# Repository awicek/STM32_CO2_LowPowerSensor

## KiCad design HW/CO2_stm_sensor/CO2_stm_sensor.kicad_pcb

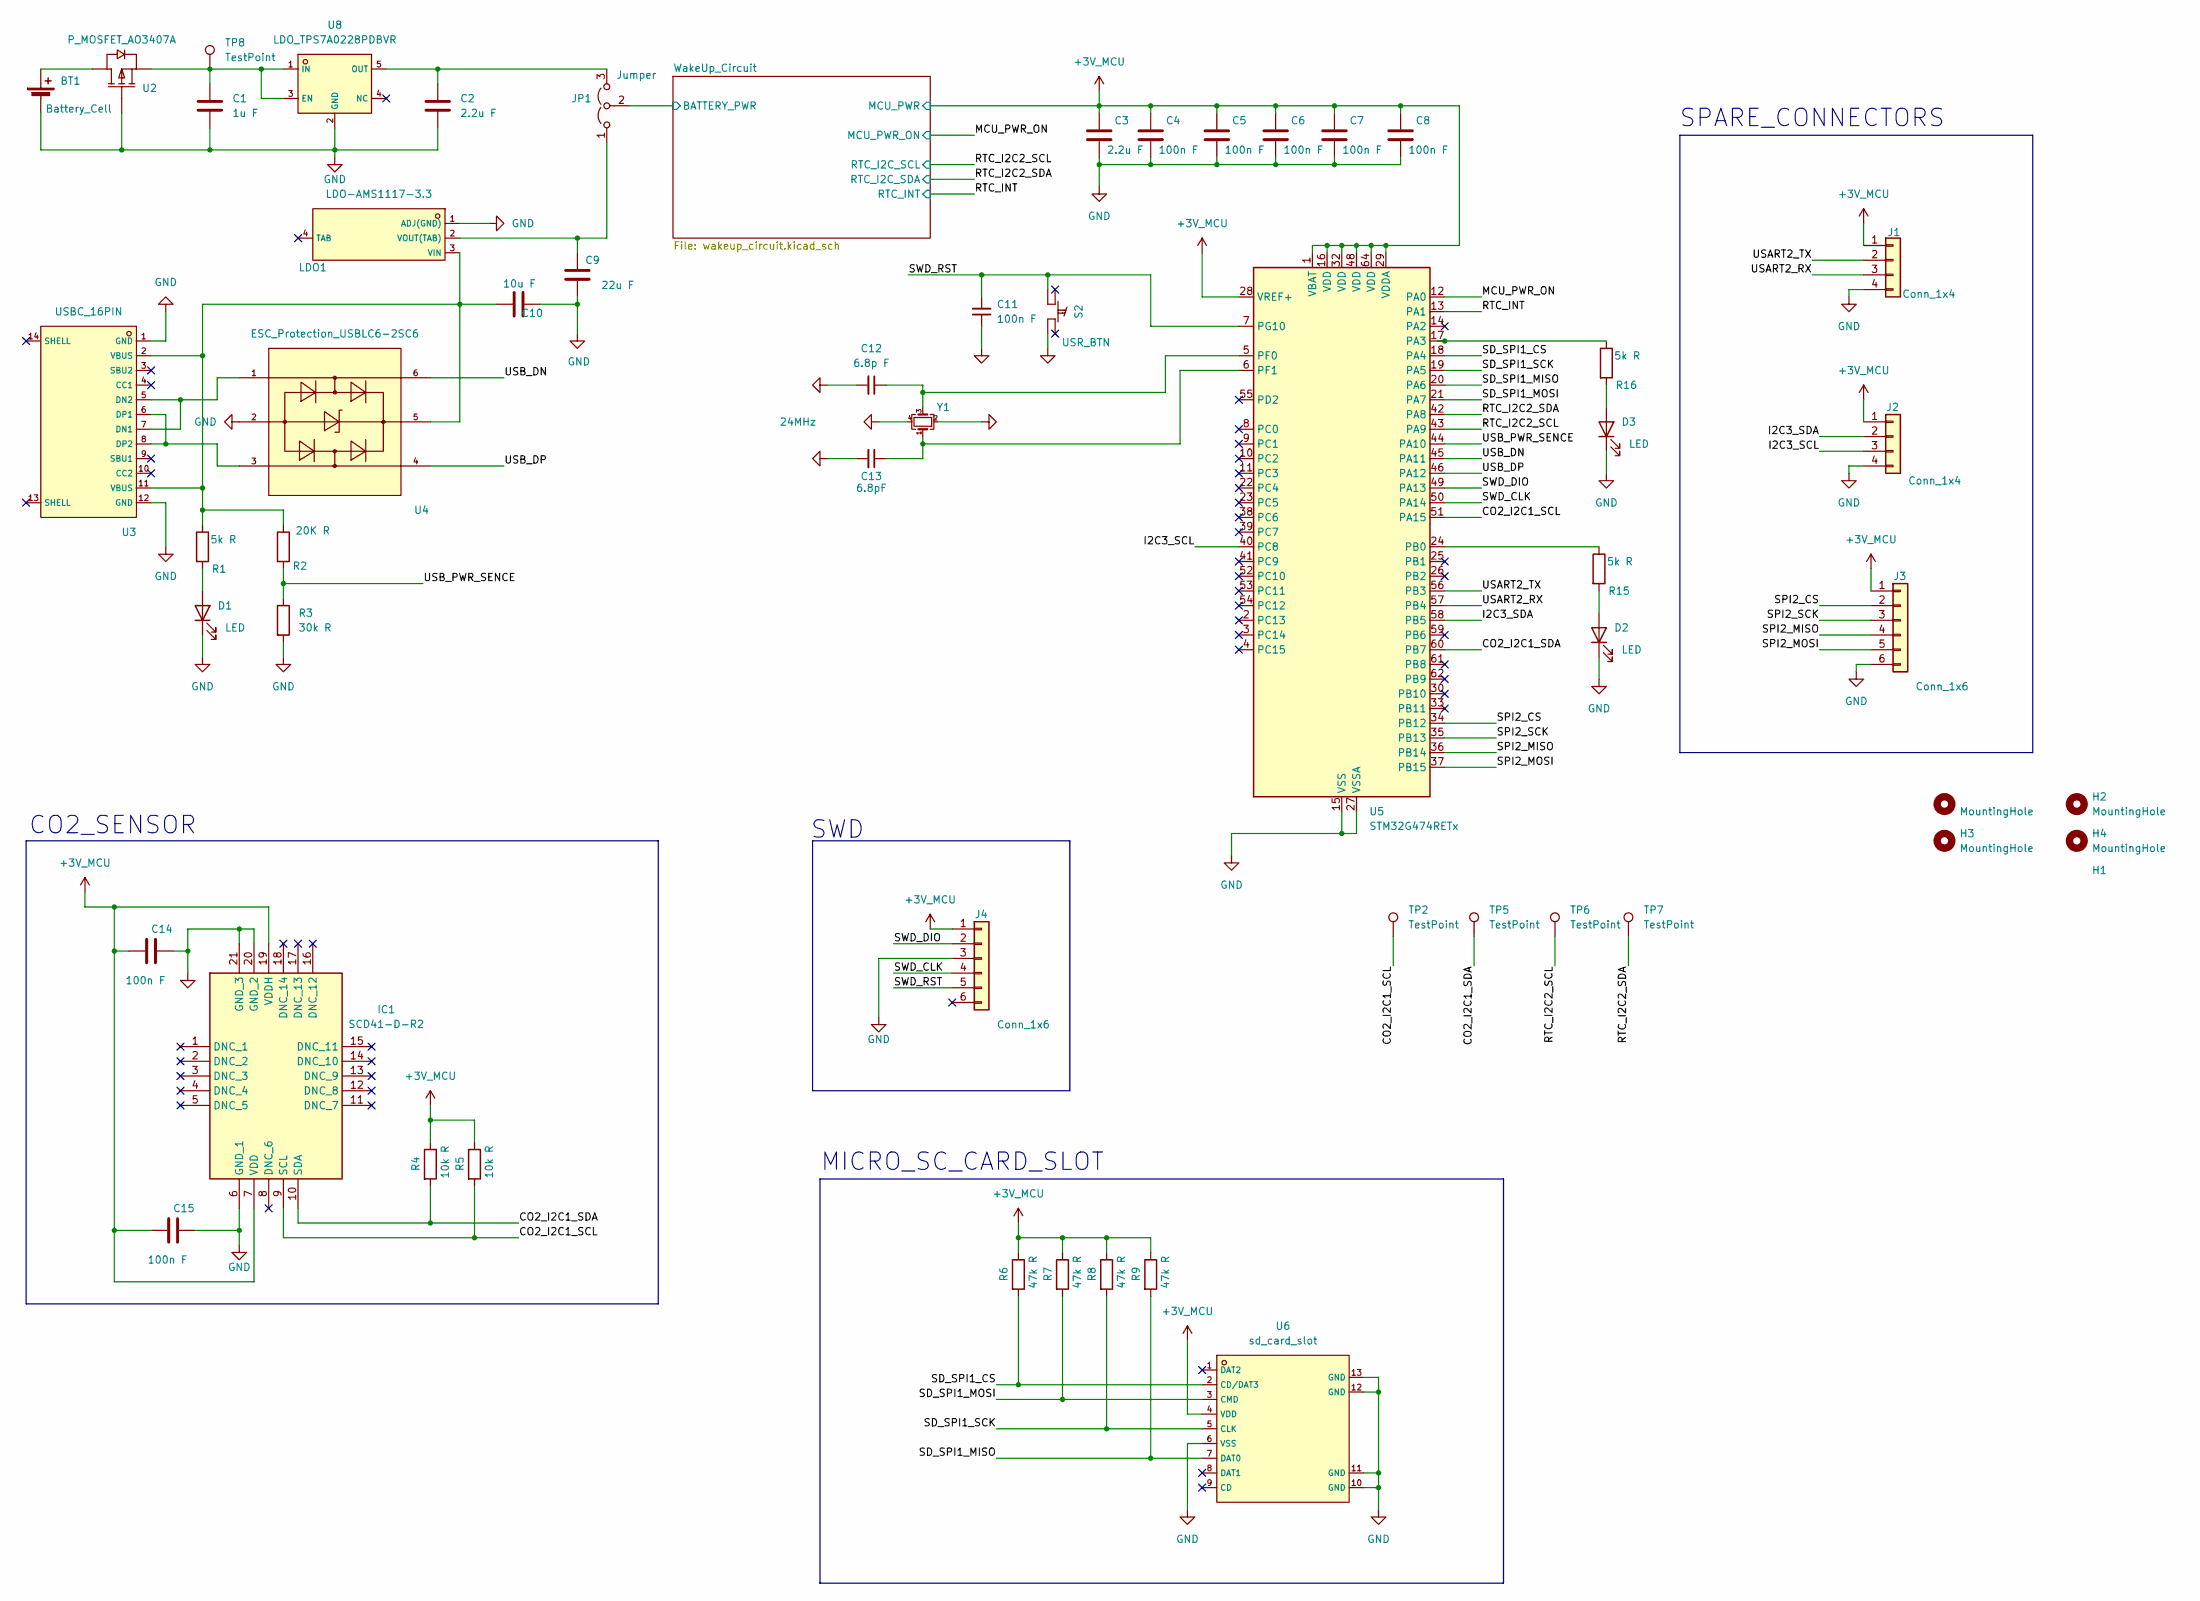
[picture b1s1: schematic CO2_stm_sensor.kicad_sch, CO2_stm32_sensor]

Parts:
BT1: Battery_Cell; BATTERY-SMD_18650-1S-L77.1-W20.7-1; LCSC Part # C7525438
C1: 1u F; C_0805_2012Metric_Pad1.18x1.45mm_HandSolder
C2, C3: 2.2u F; C_0805_2012Metric_Pad1.18x1.45mm_HandSolder
C4, C5, C6, C7, C8, C14, C15: 100n F; C_0805_2012Metric_Pad1.18x1.45mm_HandSolder
C9: 22u F; C_0805_2012Metric_Pad1.18x1.45mm_HandSolder
C10: 10u F; C_0805_2012Metric_Pad1.18x1.45mm_HandSolder
C11: 100n F; C_0805_2012Metric_Pad1.18x1.45mm_HandSolder; Mouser Part Number 80-C0805C104Z3V
C12: 6.8p F; C_0603_1608Metric_Pad1.08x0.95mm_HandSolder; LCSC Part # C1679
C13: 6.8pF; C_0603_1608Metric_Pad1.08x0.95mm_HandSolder; LCSC Part # C1679
D1, D2, D3: LED; LED_0805_2012Metric_Pad1.15x1.40mm_HandSolder
H1, H2, H3, H4: MountingHole; MountingHole_4mm
IC1: SCD41-D-R2; SCD41DR2
J1, J2: Conn_1x4; CONN-TH_4P-P2.00_S4B-PH-K-S-LF-SN; LCSC Part # C157926
J3, J4: Conn_1x6; CONN-TH_6P-P2.00_S6B-PH-K-S-LF-SN; LCSC Part # C157920
JP1: Jumper; PinHeader_1x03_P2.54mm_Vertical
LDO1: LDO-AMS1117-3.3; SOT-223-4_L6.5-W3.5-P2.30-LS7.0-BR; LCSC C347222
R1, R15, R16: 5k R; R_0805_2012Metric
R2: 20K R; R_0805_2012Metric
R3: 30k R; R_0805_2012Metric
R4, R5: 10k R; R_0805_2012Metric
R6, R7, R8, R9: 47k R; R_0805_2012Metric
S2: USR_BTN; pushbutton_EVQPUC02K; LCSC Part # C79174
TP2, TP5, TP6, TP7, TP8: TestPoint; PinHeader_1x01_P2.54mm_Vertical
U2: P_MOSFET_AO3407A; SOT-23-3_L2.9-W1.6-P1.90-LS2.8-BR; LCSC C15155
U3: USBC_16PIN; USB-C-SMD_TYPE-C-6PIN-2MD-073; LCSC C2765186
U4: ESC_Protection_USBLC6-2SC6; SOT-23-6_L2.9-W1.6-P0.95-LS2.8-BL; LCSC C7519
U5: STM32G474RETx; LQFP-64_10x10mm_P0.5mm; LCSC Part # C521608
U6: sd_card_slot; TF-SMD_TF-CARD-H1.8; LCSC C7529389
U8: LDO_TPS7A0228PDBVR; SOT-23-5_L2.9-W1.6-P0.95-LS2.8-BR; LCSC C5220176
Y1: 24MHz; CRYSTAL-SMD_4P-L2.0-W1.6-BL; LCSC Part # C37635325

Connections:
+3V_MCU: C3.1, C4.1, C5.1, C6.1, C7.1, C8.1, C14.1, C15.1, IC1.7 (VDD), IC1.19 (VDDH), J1.1, J2.1, J3.1, J4.1, R4.1, R5.1, R6.1, R7.1, R8.1, R9.1, U5.1 (VBAT), U5.16 (VDD), U5.28 (VREF+), U5.29 (VDDA), U5.32 (VDD), U5.48 (VDD), U5.64 (VDD), U6.4 (VDD); also elsewhere on the board
/CO2_I2C1_SCL: IC1.9 (SCL), R5.2, TP2.1, U5.51 (PA15)
/CO2_I2C1_SDA: IC1.10 (SDA), R4.2, TP5.1, U5.60 (PB7)
/I2C3_SCL: J2.3, U5.40 (PC8)
/I2C3_SDA: J2.2, U5.58 (PB5)
/MCU_PWR_ON: U5.12 (PA0); also elsewhere on the board
/RTC_I2C2_SCL: TP6.1, U5.43 (PA9); also elsewhere on the board
/RTC_I2C2_SDA: TP7.1, U5.42 (PA8); also elsewhere on the board
/RTC_INT: U5.13 (PA1); also elsewhere on the board
/SD_SPI1_CS: R6.2, U5.18 (PA4), U6.2 (CD/DAT3)
/SD_SPI1_MISO: R9.2, U5.20 (PA6), U6.7 (DAT0)
/SD_SPI1_MOSI: R7.2, U5.21 (PA7), U6.3 (CMD)
/SD_SPI1_SCK: R8.2, U5.19 (PA5), U6.5 (CLK)
/SPI2_CS: J3.2, U5.34 (PB12)
/SPI2_MISO: J3.4, U5.36 (PB14)
/SPI2_MOSI: J3.5, U5.37 (PB15)
/SPI2_SCK: J3.3, U5.35 (PB13)
/SWD_CLK: J4.4, U5.50 (PA14)
/SWD_DIO: J4.2, U5.49 (PA13)
/SWD_RST: C11.2, J4.5, S2.2, U5.7 (PG10)
/USART2_RX: J1.3, U5.57 (PB4)
/USART2_TX: J1.2, U5.56 (PB3)
/USB_DN: U4.6, U5.45 (PA11)
/USB_DP: U4.4, U5.46 (PA12)
/USB_PWR_SENCE: R2.2, R3.1, U5.44 (PA10)
/WakeUp_Circuit/BATTERY_PWR: JP1.2 (C); also elsewhere on the board
GND: BT1.2 (-), C1.2, C2.2, C3.2, C4.2, C5.2, C6.2, C7.2, C8.2, C9.2, C10.2, C11.1, C12.2, C13.2, C14.2, C15.2, D1.1 (K), D2.1 (K), D3.1 (K), IC1.6 (GND_1), IC1.20 (GND_2), IC1.21 (GND_3), J1.4, J2.4, J3.6, J4.3, LDO1.1 (ADJ(GND)), R3.2, S2.4, U2.1 (G), U3.1 (GND), U3.12 (GND), U4.2, U5.15 (VSS), U5.27 (VSSA), U5.31 (VSS), U5.47 (VSS), U5.63 (VSS), U6.6 (VSS), U6.10 (GND), U6.11 (GND), U6.12 (GND), U6.13 (GND), U8.2 (GND), Y1.2, Y1.4; also elsewhere on the board
unnamed: BT1.1 (+), U2.3 (D)
unnamed: D1.2 (A), R1.2
unnamed: D2.2 (A), R15.2
unnamed: D3.2 (A), R16.2
unnamed: C9.1, JP1.1 (A), LDO1.2 (VOUT(TAB))
unnamed: C2.1, JP1.3 (B), U8.5 (OUT)
unnamed: C10.1, LDO1.3 (VIN), R1.1, R2.1, U3.2 (VBUS), U3.11 (VBUS), U4.5
unnamed: C1.1, TP8.1, U2.2 (S), U8.1 (IN), U8.3 (EN)
unnamed: U3.5 (DN2), U3.7 (DN1), U4.1
unnamed: U3.6 (DP1), U3.8 (DP2), U4.3
unnamed: R16.1, U5.17 (PA3)
unnamed: R15.1, U5.24 (PB0)
unnamed: C12.1, U5.5 (PF0), Y1.3
unnamed: C13.1, U5.6 (PF1), Y1.1

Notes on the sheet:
SWD
MICRO_SC_CARD_SLOT
SPARE_CONNECTORS
CO2_SENSOR

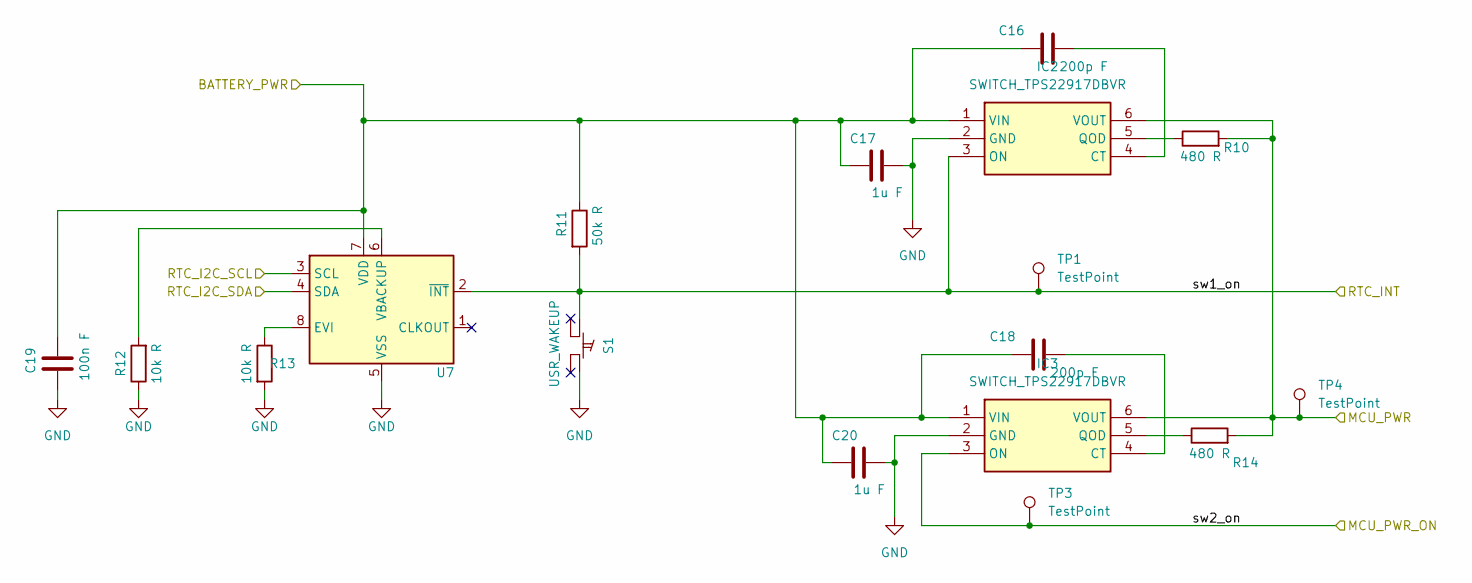
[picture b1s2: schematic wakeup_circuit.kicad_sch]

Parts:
C16, C18: 200p F; C_0805_2012Metric_Pad1.18x1.45mm_HandSolder
C17, C20: 1u F; C_0805_2012Metric_Pad1.18x1.45mm_HandSolder
C19: 100n F; C_0805_2012Metric_Pad1.18x1.45mm_HandSolder
IC2: SWITCH_TPS22917DBVR; SOT95P280X145-6N
IC3: SWITCH_TPS22917DBVR; SOT95P280X145-6N; Mouser Part Number 595-TPS22917DBVR
R10, R14: 480 R; R_0805_2012Metric
R11: 50k R; R_0805_2012Metric
R12, R13: 10k R; R_0805_2012Metric
S1: USR_WAKEUP; pushbutton_EVQPUC02K; LCSC Part # C79174
TP1, TP3, TP4: TestPoint; PinHeader_1x01_P2.54mm_Vertical
U7: MicroCrystal_C7_SON-8_1.5x3.2mm_P0.9mm

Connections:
+3V_MCU: IC2.6 (VOUT), IC3.6 (VOUT), R10.2, R14.2, TP4.1; also elsewhere on the board
/MCU_PWR_ON: IC3.3 (ON), TP3.1; also elsewhere on the board
/RTC_I2C2_SCL: U7.3 (SCL); also elsewhere on the board
/RTC_I2C2_SDA: U7.4 (SDA); also elsewhere on the board
/RTC_INT: IC2.3 (ON), R11.2, S1.1, TP1.1, U7.2 (~INT); also elsewhere on the board
/WakeUp_Circuit/BATTERY_PWR: C16.1, C17.1, C18.1, C19.1, C20.1, IC2.1 (VIN), IC3.1 (VIN), R11.1, U7.7 (VDD); also elsewhere on the board
GND: C17.2, C19.2, C20.2, IC2.2 (GND), IC3.2 (GND), R12.1, R13.2, S1.3, U7.5 (VSS); also elsewhere on the board
unnamed: C16.2, IC2.4 (CT)
unnamed: IC2.5 (QOD), R10.1
unnamed: C18.2, IC3.4 (CT)
unnamed: IC3.5 (QOD), R14.1
unnamed: R13.1, U7.8 (EVI)
unnamed: R12.2, U7.6 (VBACKUP)

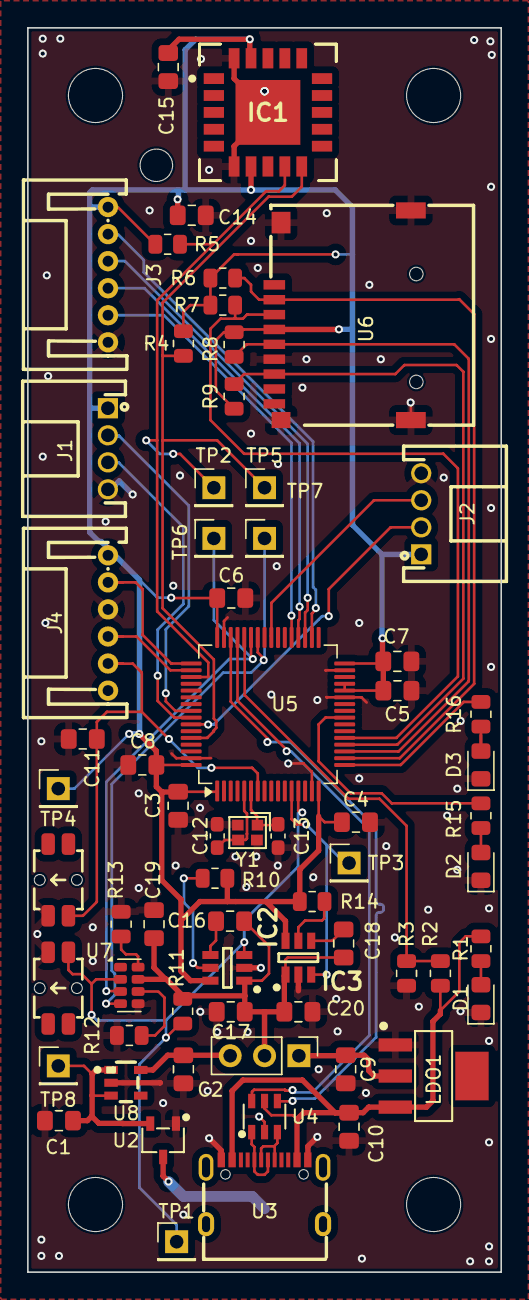
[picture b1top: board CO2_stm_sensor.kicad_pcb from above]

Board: 2 copper layers, 35.0 x 92.0 mm, 71 parts (1 on the bottom side), 47 nets.

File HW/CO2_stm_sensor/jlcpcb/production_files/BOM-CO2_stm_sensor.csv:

Comment,Designator,Footprint,LCSC,Quantity
100n F,C5,C_0805_2012Metric_Pad1.18x1.45mm_HandSolder,C49678,1
10k R,R4,R_0805_2012Metric,C17414,1
10u F,C10,C_0805_2012Metric_Pad1.18x1.45mm_HandSolder,C15850,1
1u F,C1,C_0805_2012Metric_Pad1.18x1.45mm_HandSolder,C28323,1
2.2u F,C2,C_0805_2012Metric_Pad1.18x1.45mm_HandSolder,C377773,1
200p F,C16,C_0805_2012Metric_Pad1.18x1.45mm_HandSolder,C1724,1
20K R,R2,R_0805_2012Metric,C4328,1
22u F,C9,C_0805_2012Metric_Pad1.18x1.45mm_HandSolder,C45783,1
24MHz,Y1,CRYSTAL-SMD_4P-L2.0-W1.6-BL,C37635325,1
30k R,R3,R_0805_2012Metric,C17621,1
47k R,R6,R_0805_2012Metric,C17713,1
480 R,R10,R_0805_2012Metric,C17710,1
5k R,R15,R_0805_2012Metric,C17673,1
6.8p F,C12,C_0603_1608Metric_Pad1.08x0.95mm_HandSolder,C1679,1
6.8pF,C13,C_0603_1608Metric_Pad1.08x0.95mm_HandSolder,C1679,1
Battery_Cell,BT1,BATTERY-SMD_18650-1S-L77.1-W20.7-1,C7525438,1
Conn_1x4,"J1,J2",CONN-TH_4P-P2.00_S4B-PH-K-S-LF-SN,C157926,2
Conn_1x6,"J3,J4",CONN-TH_6P-P2.00_S6B-PH-K-S-LF-SN,C157920,2
ESC_Protection_USBLC6-2SC6,U4,SOT-23-6_L2.9-W1.6-P0.95-LS2.8-BL,C7519,1
LDO-AMS1117-3.3,LDO1,SOT-223-4_L6.5-W3.5-P2.30-LS7.0-BR,C347222,1
LDO_TPS7A0228PDBVR,U8,SOT-23-5_L2.9-W1.6-P0.95-LS2.8-BR,C5220176,1
P_MOSFET_AO3407A,U2,SOT-23-3_L2.9-W1.6-P1.90-LS2.8-BR,C15155,1
STM32G474RETx,U5,LQFP-64_10x10mm_P0.5mm,C521608,1
USBC_16PIN,U3,USB-C-SMD_TYPE-C-6PIN-2MD-073,C2765186,1
USR_BTN,S2,pushbutton_EVQPUC02K,C79174,1
USR_WAKEUP,S1,pushbutton_EVQPUC02K,C79174,1
sd_card_slot,U6,TF-SMD_TF-CARD-H1.8,C7529389,1
SCD41-D-R2,IC1,SCD41DR2,,1
SWITCH_TPS22917DBVR,IC3,SOT95P280X145-6N,,1
100n F,C8,C_0805_2012Metric_Pad1.18x1.45mm_HandSolder,,1
100n F,C7,C_0805_2012Metric_Pad1.18x1.45mm_HandSolder,,1
Jumper,JP1,PinHeader_1x03_P2.54mm_Vertical,,1
~,U7,MicroCrystal_C7_SON-8_1.5x3.2mm_P0.9mm,,1
100n F,C6,C_0805_2012Metric_Pad1.18x1.45mm_HandSolder,,1
2.2u F,C3,C_0805_2012Metric_Pad1.18x1.45mm_HandSolder,,1
100n F,C19,C_0805_2012Metric_Pad1.18x1.45mm_HandSolder,,1
1u F,C20,C_0805_2012Metric_Pad1.18x1.45mm_HandSolder,,1
47k R,R8,R_0805_2012Metric,,1
LED,D2,LED_0805_2012Metric_Pad1.15x1.40mm_HandSolder,,1
SWITCH_TPS22917DBVR,IC2,SOT95P280X145-6N,,1
100n F,C14,C_0805_2012Metric_Pad1.18x1.45mm_HandSolder,,1
1u F,C17,C_0805_2012Metric_Pad1.18x1.45mm_HandSolder,,1
47k R,R7,R_0805_2012Metric,,1
480 R,R14,R_0805_2012Metric,,1
10k R,R5,R_0805_2012Metric,,1
200p F,C18,C_0805_2012Metric_Pad1.18x1.45mm_HandSolder,,1
47k R,R9,R_0805_2012Metric,,1
100n F,C11,C_0805_2012Metric_Pad1.18x1.45mm_HandSolder,,1
LED,D1,LED_0805_2012Metric_Pad1.15x1.40mm_HandSolder,,1
2k R,R1,R_0805_2012Metric,,1
100n F,C4,C_0805_2012Metric_Pad1.18x1.45mm_HandSolder,,1
10k R,R13,R_0805_2012Metric,,1
100n F,C15,C_0805_2012Metric_Pad1.18x1.45mm_HandSolder,,1
50k R,R11,R_0805_2012Metric,,1
10k R,R12,R_0805_2012Metric,,1
TestPoint,TP8,PinHeader_1x01_P2.54mm_Vertical,,1
TestPoint,TP7,PinHeader_1x01_P2.54mm_Vertical,,1
TestPoint,TP6,PinHeader_1x01_P2.54mm_Vertical,,1
TestPoint,TP5,PinHeader_1x01_P2.54mm_Vertical,,1
TestPoint,TP4,PinHeader_1x01_P2.54mm_Vertical,,1
TestPoint,TP3,PinHeader_1x01_P2.54mm_Vertical,,1
TestPoint,TP2,PinHeader_1x01_P2.54mm_Vertical,,1
TestPoint,TP1,PinHeader_1x01_P2.54mm_Vertical,,1
5k R,R16,R_0805_2012Metric,,1
LED,D3,LED_0805_2012Metric_Pad1.15x1.40mm_HandSolder,,1

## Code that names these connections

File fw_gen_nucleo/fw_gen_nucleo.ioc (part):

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Mcu.Name=STM32G474R(B-C-E)Tx
Mcu.Package=LQFP64
Mcu.UserName=STM32G474RETx
PA13.GPIOParameters=GPIO_Label
PA13.GPIO_Label=T_SWDIO
PA13.Signal=SYS_JTMS-SWDIO
PA14.GPIOParameters=GPIO_Label
PA14.GPIO_Label=T_SWCLK
PA14.Signal=SYS_JTCK-SWCLK
PA15.Mode=I2C
PA15.Signal=I2C1_SCL
PA2.Mode=Asynchronous
PA2.Signal=USART2_TX
PA3.Mode=Asynchronous
PA3.Signal=USART2_RX
PA4.Signal=GPIO_Output
PA5.Mode=Full_Duplex_Master
PA5.Signal=SPI1_SCK
PA6.Mode=Full_Duplex_Master
PA6.Signal=SPI1_MISO
PA7.Mode=Full_Duplex_Master
PA7.Signal=SPI1_MOSI
PA8.Mode=I2C
PA8.Signal=I2C2_SDA
PB1.GPIOParameters=PinState,GPIO_PuPd
PB1.GPIO_PuPd=GPIO_PULLUP
PB1.PinState=GPIO_PIN_SET
PB1.Signal=GPIO_Output
PB3.GPIOParameters=GPIO_Label
PB3.GPIO_Label=T_SWO
PB3.Signal=SYS_JTDO-SWO
PB7.Mode=I2C
PB7.Signal=I2C1_SDA
PC14-OSC32_IN.GPIOParameters=GPIO_Label
PC14-OSC32_IN.GPIO_Label=RCC_OSC32_IN
PC14-OSC32_IN.Signal=RCC_OSC32_IN
PC15-OSC32_OUT.GPIOParameters=GPIO_Label
PC15-OSC32_OUT.GPIO_Label=RCC_OSC32_OUT
PC15-OSC32_OUT.Signal=RCC_OSC32_OUT
PC4.Mode=I2C
PC4.Signal=I2C2_SCL
PF0-OSC_IN.GPIOParameters=GPIO_Label
PF0-OSC_IN.GPIO_Label=RCC_OSC_IN
PF0-OSC_IN.Signal=RCC_OSC_IN
PF1-OSC_OUT.GPIOParameters=GPIO_Label
PF1-OSC_OUT.GPIO_Label=RCC_OSC_OUT
PF1-OSC_OUT.Signal=RCC_OSC_OUT
RCC.HSE_VALUE=24000000
RCC.SYSCLKFreq_VALUE=16000000
board=NUCLEO-G474RE
boardIOC=true

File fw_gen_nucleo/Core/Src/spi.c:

/* USER CODE BEGIN Header */
/**
  ******************************************************************************
  * @file    spi.c
  * @brief   This file provides code for the configuration
  *          of the SPI instances.
  ******************************************************************************
  * @attention
  *
  * Copyright (c) 2026 STMicroelectronics.
  * All rights reserved.
  *
  * This software is licensed under terms that can be found in the LICENSE file
  * in the root directory of this software component.
  * If no LICENSE file comes with this software, it is provided AS-IS.
  *
  ******************************************************************************
  */
/* USER CODE END Header */
/* Includes ------------------------------------------------------------------*/
#include "spi.h"

/* USER CODE BEGIN 0 */

/* USER CODE END 0 */

SPI_HandleTypeDef hspi1;
SPI_HandleTypeDef hspi2;

/* SPI1 init function */
void MX_SPI1_Init(void)
{

  /* USER CODE BEGIN SPI1_Init 0 */

  /* USER CODE END SPI1_Init 0 */

  /* USER CODE BEGIN SPI1_Init 1 */

  /* USER CODE END SPI1_Init 1 */
  hspi1.Instance = SPI1;
  hspi1.Init.Mode = SPI_MODE_MASTER;
  hspi1.Init.Direction = SPI_DIRECTION_2LINES;
  hspi1.Init.DataSize = SPI_DATASIZE_8BIT;
  hspi1.Init.CLKPolarity = SPI_POLARITY_LOW;
  hspi1.Init.CLKPhase = SPI_PHASE_1EDGE;
  hspi1.Init.NSS = SPI_NSS_SOFT;
  hspi1.Init.BaudRatePrescaler = SPI_BAUDRATEPRESCALER_128;
  hspi1.Init.FirstBit = SPI_FIRSTBIT_MSB;
  hspi1.Init.TIMode = SPI_TIMODE_DISABLE;
  hspi1.Init.CRCCalculation = SPI_CRCCALCULATION_DISABLE;
  hspi1.Init.CRCPolynomial = 7;
  hspi1.Init.CRCLength = SPI_CRC_LENGTH_DATASIZE;
  hspi1.Init.NSSPMode = SPI_NSS_PULSE_ENABLE;
  if (HAL_SPI_Init(&hspi1) != HAL_OK)
  {
    Error_Handler();
  }
  /* USER CODE BEGIN SPI1_Init 2 */

  /* USER CODE END SPI1_Init 2 */

}
/* SPI2 init function */
void MX_SPI2_Init(void)
{

  /* USER CODE BEGIN SPI2_Init 0 */

  /* USER CODE END SPI2_Init 0 */

  /* USER CODE BEGIN SPI2_Init 1 */

  /* USER CODE END SPI2_Init 1 */
  hspi2.Instance = SPI2;
  hspi2.Init.Mode = SPI_MODE_MASTER;
  hspi2.Init.Direction = SPI_DIRECTION_2LINES;
  hspi2.Init.DataSize = SPI_DATASIZE_8BIT;
  hspi2.Init.CLKPolarity = SPI_POLARITY_LOW;
  hspi2.Init.CLKPhase = SPI_PHASE_1EDGE;
  hspi2.Init.NSS = SPI_NSS_SOFT;
  hspi2.Init.BaudRatePrescaler = SPI_BAUDRATEPRESCALER_256;
  hspi2.Init.FirstBit = SPI_FIRSTBIT_MSB;
  hspi2.Init.TIMode = SPI_TIMODE_DISABLE;
  hspi2.Init.CRCCalculation = SPI_CRCCALCULATION_DISABLE;
  hspi2.Init.CRCPolynomial = 7;
  hspi2.Init.CRCLength = SPI_CRC_LENGTH_DATASIZE;
  hspi2.Init.NSSPMode = SPI_NSS_PULSE_ENABLE;
  if (HAL_SPI_Init(&hspi2) != HAL_OK)
  {
    Error_Handler();
  }
  /* USER CODE BEGIN SPI2_Init 2 */

  /* USER CODE END SPI2_Init 2 */

}

void HAL_SPI_MspInit(SPI_HandleTypeDef* spiHandle)
{

  GPIO_InitTypeDef GPIO_InitStruct = {0};
  if(spiHandle->Instance==SPI1)
  {
  /* USER CODE BEGIN SPI1_MspInit 0 */

  /* USER CODE END SPI1_MspInit 0 */
    /* SPI1 clock enable */
    __HAL_RCC_SPI1_CLK_ENABLE();

    __HAL_RCC_GPIOA_CLK_ENABLE();
    /**SPI1 GPIO Configuration
    PA5     ------> SPI1_SCK
    PA6     ------> SPI1_MISO
    PA7     ------> SPI1_MOSI
    */
    GPIO_InitStruct.Pin = GPIO_PIN_5|GPIO_PIN_6|GPIO_PIN_7;
    GPIO_InitStruct.Mode = GPIO_MODE_AF_PP;
    GPIO_InitStruct.Pull = GPIO_NOPULL;
    GPIO_InitStruct.Speed = GPIO_SPEED_FREQ_LOW;
    GPIO_InitStruct.Alternate = GPIO_AF5_SPI1;
    HAL_GPIO_Init(GPIOA, &GPIO_InitStruct);

  /* USER CODE BEGIN SPI1_MspInit 1 */

  /* USER CODE END SPI1_MspInit 1 */
  }
  else if(spiHandle->Instance==SPI2)
  {
  /* USER CODE BEGIN SPI2_MspInit 0 */

  /* USER CODE END SPI2_MspInit 0 */
    /* SPI2 clock enable */
    __HAL_RCC_SPI2_CLK_ENABLE();

    __HAL_RCC_GPIOB_CLK_ENABLE();
    /**SPI2 GPIO Configuration
    PB13     ------> SPI2_SCK
    PB14     ------> SPI2_MISO
    PB15     ------> SPI2_MOSI
    */
    GPIO_InitStruct.Pin = GPIO_PIN_13|GPIO_PIN_14|GPIO_PIN_15;
    GPIO_InitStruct.Mode = GPIO_MODE_AF_PP;
    GPIO_InitStruct.Pull = GPIO_NOPULL;
    GPIO_InitStruct.Speed = GPIO_SPEED_FREQ_LOW;
    GPIO_InitStruct.Alternate = GPIO_AF5_SPI2;
    HAL_GPIO_Init(GPIOB, &GPIO_InitStruct);

  /* USER CODE BEGIN SPI2_MspInit 1 */

  /* USER CODE END SPI2_MspInit 1 */
  }
}

void HAL_SPI_MspDeInit(SPI_HandleTypeDef* spiHandle)
{

  if(spiHandle->Instance==SPI1)
  {
  /* USER CODE BEGIN SPI1_MspDeInit 0 */

  /* USER CODE END SPI1_MspDeInit 0 */
    /* Peripheral clock disable */
    __HAL_RCC_SPI1_CLK_DISABLE();

    /**SPI1 GPIO Configuration
    PA5     ------> SPI1_SCK
    PA6     ------> SPI1_MISO
    PA7     ------> SPI1_MOSI
    */
    HAL_GPIO_DeInit(GPIOA, GPIO_PIN_5|GPIO_PIN_6|GPIO_PIN_7);

  /* USER CODE BEGIN SPI1_MspDeInit 1 */

  /* USER CODE END SPI1_MspDeInit 1 */
  }
  else if(spiHandle->Instance==SPI2)
  {
  /* USER CODE BEGIN SPI2_MspDeInit 0 */

  /* USER CODE END SPI2_MspDeInit 0 */
    /* Peripheral clock disable */
    __HAL_RCC_SPI2_CLK_DISABLE();

    /**SPI2 GPIO Configuration
    PB13     ------> SPI2_SCK
    PB14     ------> SPI2_MISO
    PB15     ------> SPI2_MOSI
    */
    HAL_GPIO_DeInit(GPIOB, GPIO_PIN_13|GPIO_PIN_14|GPIO_PIN_15);

  /* USER CODE BEGIN SPI2_MspDeInit 1 */

  /* USER CODE END SPI2_MspDeInit 1 */
  }
}

/* USER CODE BEGIN 1 */

/* USER CODE END 1 */

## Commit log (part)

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2025-09-22 init
2026-01-13 update gitignore
2026-04-13 setup firmware and _fw_gen folders
2026-04-23 genration for the spi sd card
2026-04-23 gen folder changes
2026-04-25 stm32g4 init
2026-04-26 co2 readout
2026-04-26 spi-sd-card read/write works
2026-04-29 shchematic v0.0 done
2026-04-30 hw v1.0
2026-04-30 FIRST ORDER git statusgit status
2026-05-01 LDO GND connected and pwr led rotated in the pcb design
2026-05-01 printf
2026-05-01 remove HW from firmware only branch
2026-05-02 preparation for gpio driver
2026-05-02 add pulldowns to the usb cc1/2 pins
2026-05-04 some gen files
2026-05-04 gel ll iic
2026-05-04 custom iic driver
2026-05-05 basic of co2sensor class
2026-05-06 iic readout fucked up
2026-05-06 co2 driver v0
2026-05-13 some minor harware change
2026-05-13 spi ll gen
2026-05-20 spi tx
2026-05-20 git ignore
2026-05-20 assembly file
2026-05-21 co2 sensors and leds works
2026-05-21 sd card hal on the same pins as co2hardware
2026-05-21 preparation for the sd_card
2026-05-21 sd does not work
2026-05-22 wakeup circuit and rtc lives
2026-05-22 rtc wakeup works
2026-05-23 iic1 is dead
2026-05-23 spaggeti readout and spi write
2026-06-07 power test1
2026-06-11 power saving tests
